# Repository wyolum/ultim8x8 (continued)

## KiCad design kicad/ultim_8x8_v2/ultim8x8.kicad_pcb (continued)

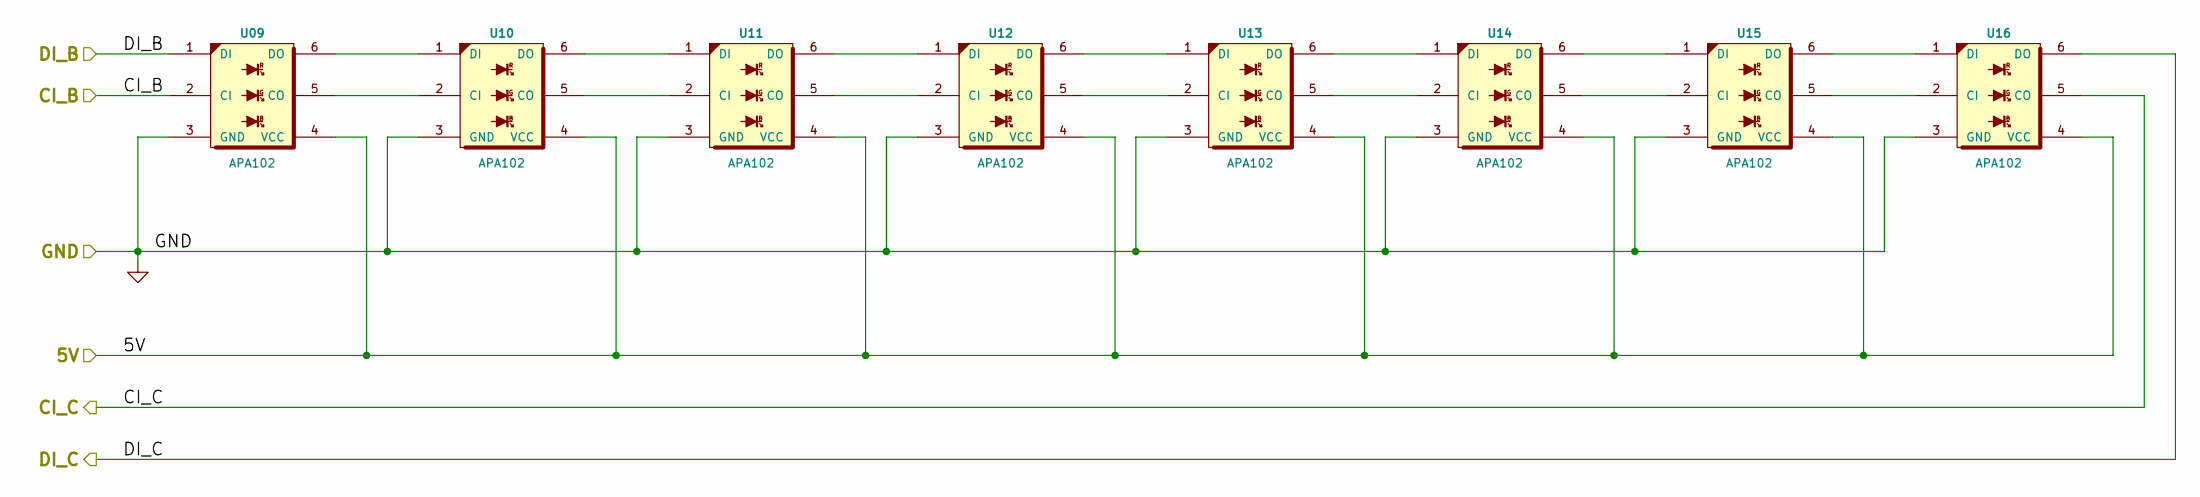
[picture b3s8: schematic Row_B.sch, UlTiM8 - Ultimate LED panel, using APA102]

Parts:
U09, U10, U11, U12, U13, U14, U15, U16: APA102

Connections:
/5V: U09.4 (VCC), U10.4 (VCC), U11.4 (VCC), U12.4 (VCC), U13.4 (VCC), U14.4 (VCC), U15.4 (VCC), U16.4 (VCC); also elsewhere on the board
/CI_B: U09.2 (CI); also elsewhere on the board
/CI_C: U16.5 (CO); also elsewhere on the board
/DI_B: U09.1 (DI); also elsewhere on the board
/DI_C: U16.6 (DO); also elsewhere on the board
GND: U09.3 (GND), U10.3 (GND), U11.3 (GND), U12.3 (GND), U13.3 (GND), U14.3 (GND), U15.3 (GND), U16.3 (GND); also elsewhere on the board
unnamed: U09.5 (CO), U10.2 (CI)
unnamed: U09.6 (DO), U10.1 (DI)
unnamed: U10.5 (CO), U11.2 (CI)
unnamed: U10.6 (DO), U11.1 (DI)
unnamed: U11.5 (CO), U12.2 (CI)
unnamed: U11.6 (DO), U12.1 (DI)
unnamed: U12.5 (CO), U13.2 (CI)
unnamed: U12.6 (DO), U13.1 (DI)
unnamed: U13.5 (CO), U14.2 (CI)
unnamed: U13.6 (DO), U14.1 (DI)
unnamed: U14.5 (CO), U15.2 (CI)
unnamed: U14.6 (DO), U15.1 (DI)
unnamed: U15.5 (CO), U16.2 (CI)
unnamed: U15.6 (DO), U16.1 (DI)

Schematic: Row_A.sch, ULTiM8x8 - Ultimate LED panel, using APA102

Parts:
C1: 100nF; c_0805
C2: 47uF 20V; c_2917
U01, U02, U03, U04, U07, U08: APA102
U05: APA102; APA102_U05
U06: APA102; APA102_U06

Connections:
/5V: C1.2, C2.1 (+), U01.4 (VCC), U02.4 (VCC), U03.4 (VCC), U04.4 (VCC), U05.4 (VCC), U06.4 (VCC), U07.4 (VCC), U08.4 (VCC); also elsewhere on the board
/CI_A: U01.2 (CI); also elsewhere on the board
/CI_B: U08.5 (CO); also elsewhere on the board
/DI_A: U01.1 (DI); also elsewhere on the board
/DI_B: U08.6 (DO); also elsewhere on the board
GND: C1.1, C2.2 (-), U01.3 (GND), U02.3 (GND), U03.3 (GND), U04.3 (GND), U05.3 (GND), U06.3 (GND), U07.3 (GND), U08.3 (GND); also elsewhere on the board
unnamed: U01.5 (CO), U02.2 (CI)
unnamed: U01.6 (DO), U02.1 (DI)
unnamed: U02.5 (CO), U03.2 (CI)
unnamed: U02.6 (DO), U03.1 (DI)
unnamed: U03.5 (CO), U04.2 (CI)
unnamed: U03.6 (DO), U04.1 (DI)
unnamed: U04.5 (CO), U05.2 (CI)
unnamed: U04.6 (DO), U05.1 (DI)
unnamed: U05.5 (CO), U06.2 (CI)
unnamed: U05.6 (DO), U06.1 (DI)
unnamed: U06.5 (CO), U07.2 (CI)
unnamed: U06.6 (DO), U07.1 (DI)
unnamed: U07.5 (CO), U08.2 (CI)
unnamed: U07.6 (DO), U08.1 (DI)

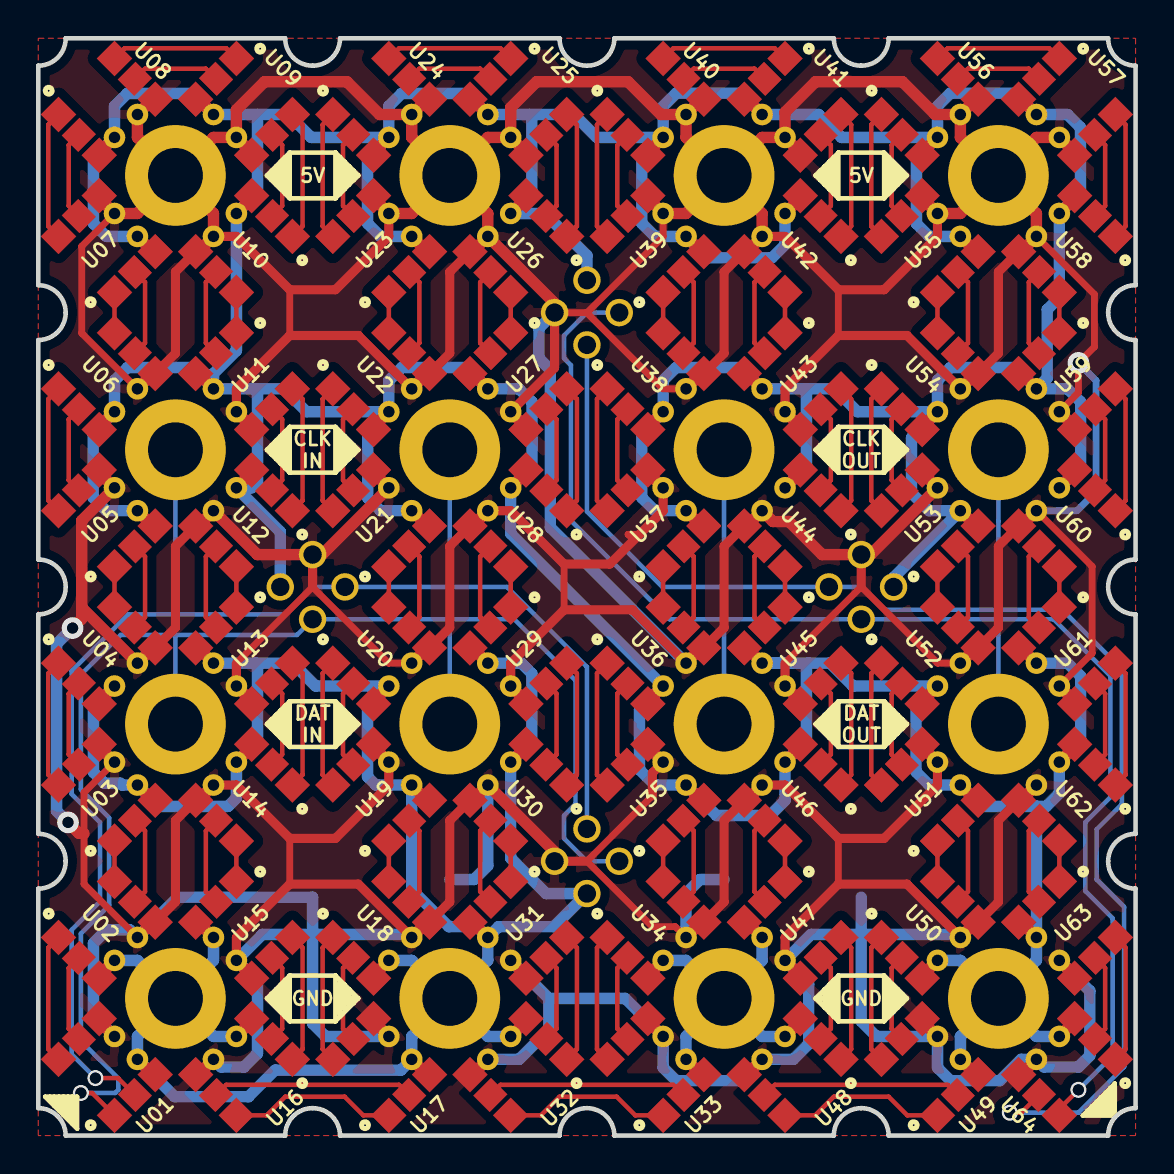
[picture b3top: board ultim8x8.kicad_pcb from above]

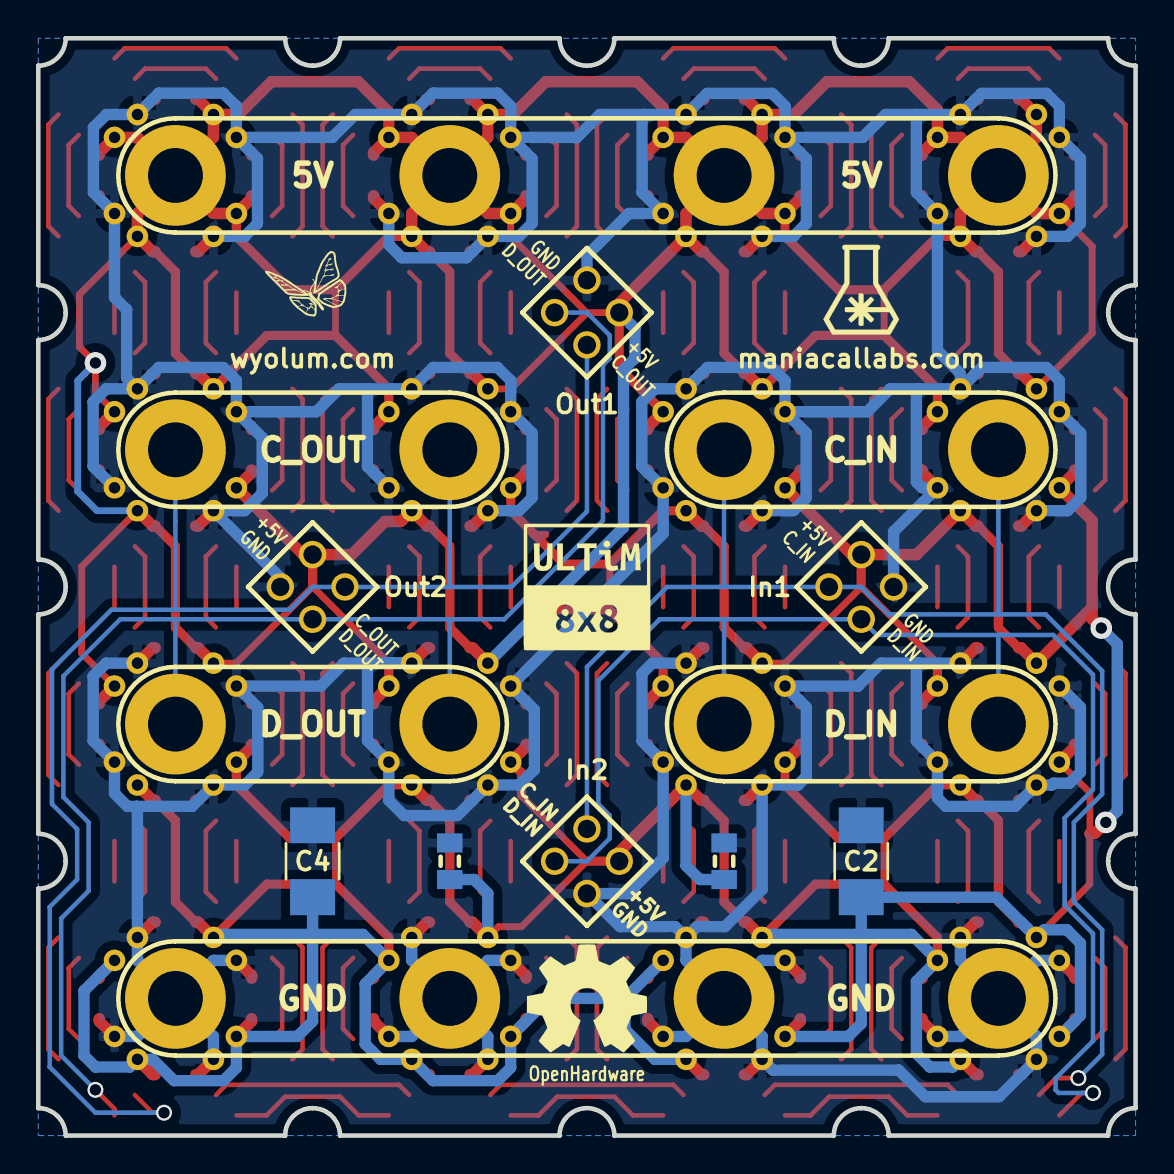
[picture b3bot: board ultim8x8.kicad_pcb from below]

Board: 2 copper layers, 61.0 x 61.0 mm, 92 parts (20 on the bottom side), 132 nets.

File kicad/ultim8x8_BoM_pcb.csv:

"Id";"Designator";"Package";"Quantity";"Designation";"Supplier and ref";
1;"L1";"logo_ultim8x8";1;"ULTiM8x8";;;
2;"P3";"PowerIn_stud";1;"5V";;;
3;"P4";"PowerIn_stud";1;"GND";;;
4;"C3,C1";"c_0805";2;"100nF";;;
5;"C2,C4";"c_2917";2;"47uF 20V";;;
6;"P6";"header_3pos_smd_male";1;"Output2";;;
7;"P5";"header_3pos_smd_male";1;"Input2";;;
8;"P2";"header_3pos_smd_male";1;"Output1";;;
9;"P1";"header_3pos_smd_male";1;"Input1";;;
10;"L2";"OSHW_6mm";1;"OSHW";;;
11;"L3";"logo_wyo_butterfly";1;"Wyolum";;;
12;"L4";"logo_MLlabs";1;"Maniacal Labs";;;
13;"U05";"APA102_U05";1;"APA102";;;
14;"U06";"APA102_U06";1;"APA102";;;
15;"U11";"APA102_U11";1;"APA102";;;
16;"U12";"APA102_U12";1;"APA102";;;
17;"U19";"APA102_U19";1;"APA102";;;
18;"U38";"APA102_U38";1;"APA102";;;
19;"U43";"APA102_U43";1;"APA102";;;
20;"U53";"APA102_U53";1;"APA102";;;
21;"U54";"APA102_U54";1;"APA102";;;
22;"U59";"APA102_U59";1;"APA102";;;
23;"U60";"APA102_U60";1;"APA102";;;
24;"U64,U49,U48,U33,U32,U17,U16,U01,U04,U02,U03,U07,U08,U09,U10,U13,U14,U15,U18,U20,U21,U22,U23,U24,U25,U26,U27,U28,U29,U30,U31,U34,U35,U36,U37,U39,U40,U41,U42,U44,U45,U46,U47,U50,U51,U52,U55,U56,U57,U58,U61,U62,U63";"APA102";53;"APA102";;;

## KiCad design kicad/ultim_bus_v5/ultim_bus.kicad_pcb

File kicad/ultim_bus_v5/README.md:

# ultim_bus

A PCB "bus bar" to allow three ultim8x8 modules to be connected easily. Mouse bites allow it to be snapped off easily. With some imagination, can be used to expand to larger matrices.

The first panel can be populated with a Huzzah. There are six SMD switches connected to 14, 12, 13, 15, 0, 16, 2 on the Huzzah, with pull up resistors (SMD 0805). Switch functions can be arbitrarily assigned in code.

License
-------
[CERN Open Hardware Licence v1.2 ]

[CERN Open Hardware Licence v1.2 ]:http://www.ohwr.org/attachments/2388/cern_ohl_v_1_2.txt

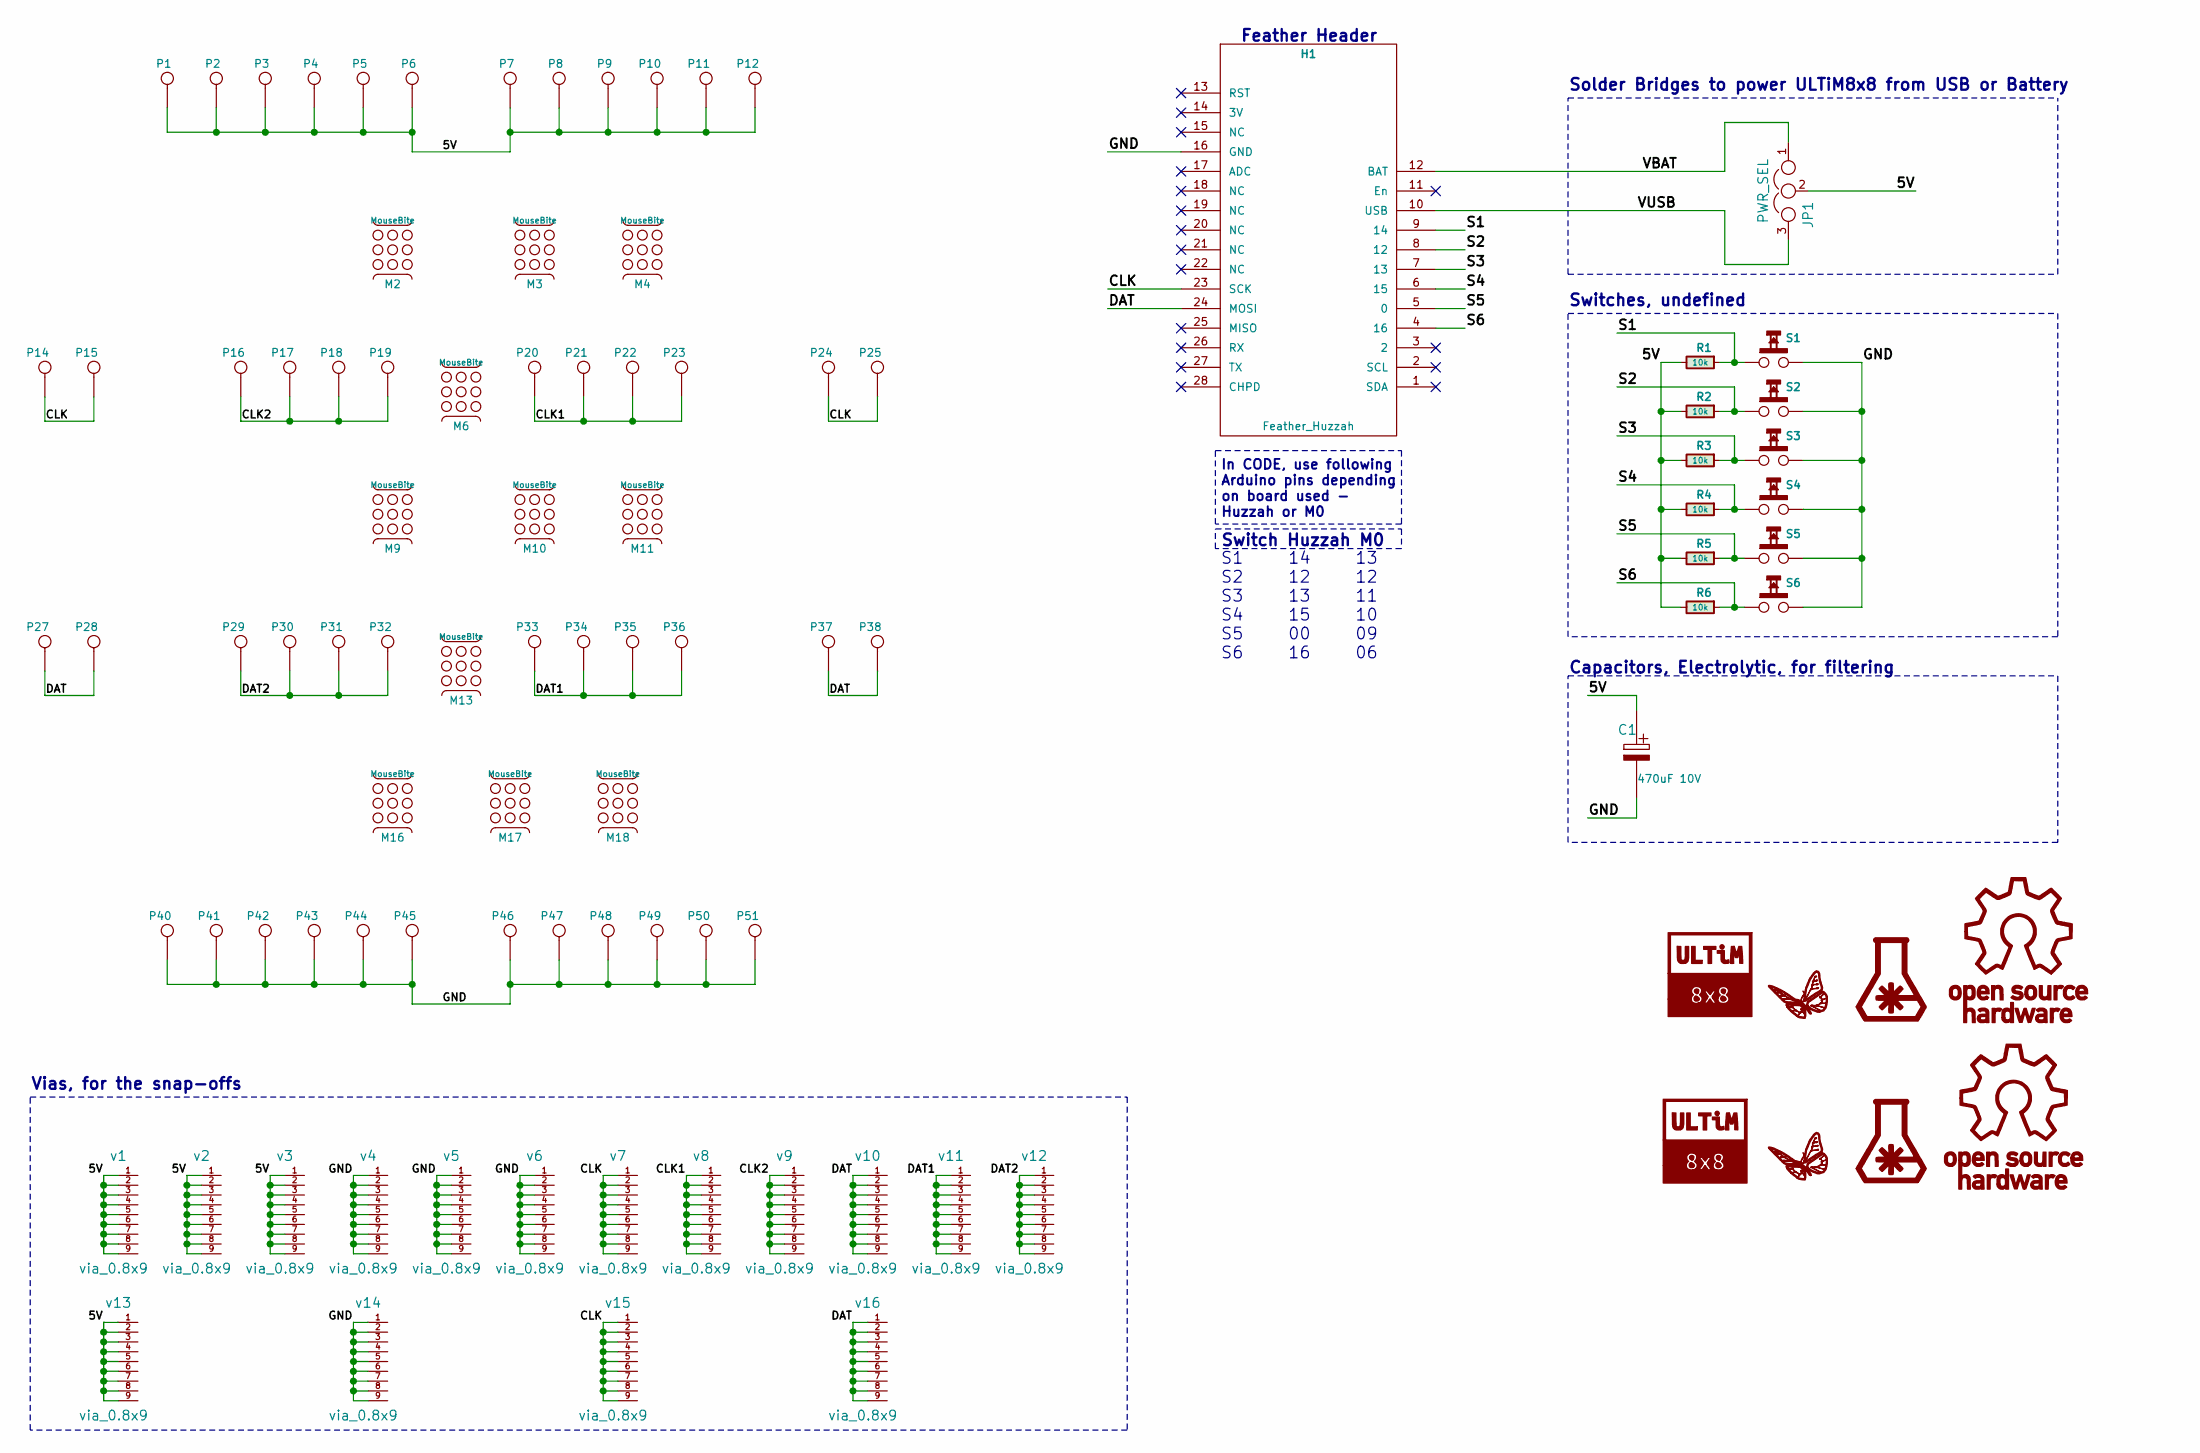
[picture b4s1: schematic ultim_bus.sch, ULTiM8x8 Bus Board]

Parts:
C1: 470uF 10V; cap_pol_rad3
H1: Feather_Huzzah; FEATHER_Huzzah
JP1: PWR_SEL; switch_spdt
L1, L2: OSHW; OSHW_6mm
L3, L4: LOGO_WL; logo_wyo_butterfly_small
L7, L8: LOGO_ML; logo_MLlabs_small
L11, L12: LOGO_U88; logo_ultim8x8_small
M2, M3, M4, M9, M10, M11, M16, M17, M18: MouseBite; mouse-bite-5.08mm-slot
M6, M13: MouseBite; mouse-bite-2.54mm-slot
P1, P4, P5, P8, P9, P12, P15, P16, P19, P20, P23, P24, P28, P29, P32, P33, P36, P37, P40, P43, P44, P47, P48, P51: CONN_1; Screw_SqPad
P2, P3, P6, P7, P10, P11, P14, P17, P18, P21, P22, P25, P27, P30, P31, P34, P35, P38, P41, P42, P45, P46, P49, P50: CONN_1; Screw
R1, R2, R3, R4, R5, R6: 10k; r_0805
S1, S2, S3, S4, S5, S6: SPST-M-2; SW-PB
v1, v2, v3, v4, v5, v6, v7, v8, v9, v10, v11, v12, v13, v14, v15, v16: via_0.8x9

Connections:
/5V: C1.1 (+), JP1.2, P1.1, P2.1, P3.1, P4.1, P5.1, P6.1, P7.1, P8.1, P9.1, P10.1, P11.1, P12.1, R1.2, R2.2, R3.2, R4.2, R5.2, R6.2, v1.1, v1.2, v1.3, v1.4, v1.5, v1.6, v1.7, v1.8, v1.9, v2.1, v2.2, v2.3, v2.4, v2.5, v2.6, v2.7, v2.8, v2.9, v3.1, v3.2, v3.3, v3.4, v3.5, v3.6, v3.7, v3.8, v3.9, v13.1, v13.2, v13.3, v13.4, v13.5, v13.6, v13.7, v13.8, v13.9
/CLK: H1.23 (SCK), P14.1, P15.1, P24.1, P25.1, v7.1, v7.2, v7.3, v7.4, v7.5, v7.6, v7.7, v7.8, v7.9, v15.1, v15.2, v15.3, v15.4, v15.5, v15.6, v15.7, v15.8, v15.9
/CLK1: P20.1, P21.1, P22.1, P23.1, v8.1, v8.2, v8.3, v8.4, v8.5, v8.6, v8.7, v8.8, v8.9
/CLK2: P16.1, P17.1, P18.1, P19.1, v9.1, v9.2, v9.3, v9.4, v9.5, v9.6, v9.7, v9.8, v9.9
/DAT: H1.24 (MOSI), P27.1, P28.1, P37.1, P38.1, v10.1, v10.2, v10.3, v10.4, v10.5, v10.6, v10.7, v10.8, v10.9, v16.1, v16.2, v16.3, v16.4, v16.5, v16.6, v16.7, v16.8, v16.9
/DAT1: P33.1, P34.1, P35.1, P36.1, v11.1, v11.2, v11.3, v11.4, v11.5, v11.6, v11.7, v11.8, v11.9
/DAT2: P29.1, P30.1, P31.1, P32.1, v12.1, v12.2, v12.3, v12.4, v12.5, v12.6, v12.7, v12.8, v12.9
/GND: C1.2 (-), H1.16 (GND), P40.1, P41.1, P42.1, P43.1, P44.1, P45.1, P46.1, P47.1, P48.1, P49.1, P50.1, P51.1, S1.2, S2.2, S3.2, S4.2, S5.2, S6.2, v4.1, v4.2, v4.3, v4.4, v4.5, v4.6, v4.7, v4.8, v4.9, v5.1, v5.2, v5.3, v5.4, v5.5, v5.6, v5.7, v5.8, v5.9, v6.1, v6.2, v6.3, v6.4, v6.5, v6.6, v6.7, v6.8, v6.9, v14.1, v14.2, v14.3, v14.4, v14.5, v14.6, v14.7, v14.8, v14.9
/S1: H1.9 (14), R1.1, S1.1
/S2: H1.8 (12), R2.1, S2.1
/S3: H1.7 (13), R3.1, S3.1
/S4: H1.6 (15), R4.1, S4.1
/S5: H1.5 (0), R5.1, S5.1
/S6: H1.4 (16), R6.1, S6.1
/VBAT: H1.12 (BAT), JP1.1
/VUSB: H1.10 (USB), JP1.3

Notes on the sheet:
Solder Bridges to power ULTiM8x8 from USB or Battery
Feather Header
Switches, undefined
Vias, for the snap-offs
Capacitors, Electrolytic, for filtering
Switch Huzzah M0
S1 14 13 S2 12 12 S3 13 11 S4 15 10 S5 00 09 S6 16 06
In CODE, use following Arduino pins depending on board used - Huzzah or M0

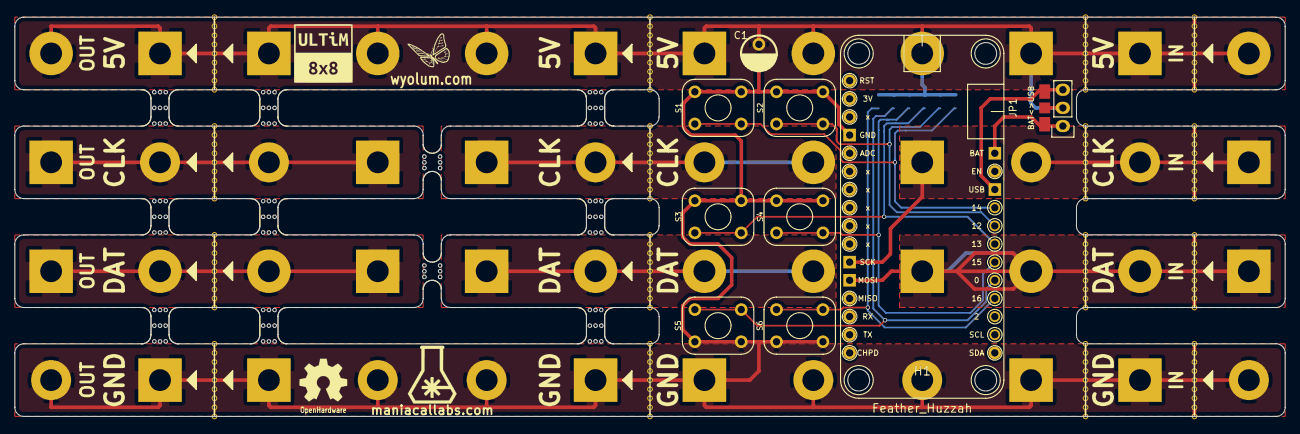
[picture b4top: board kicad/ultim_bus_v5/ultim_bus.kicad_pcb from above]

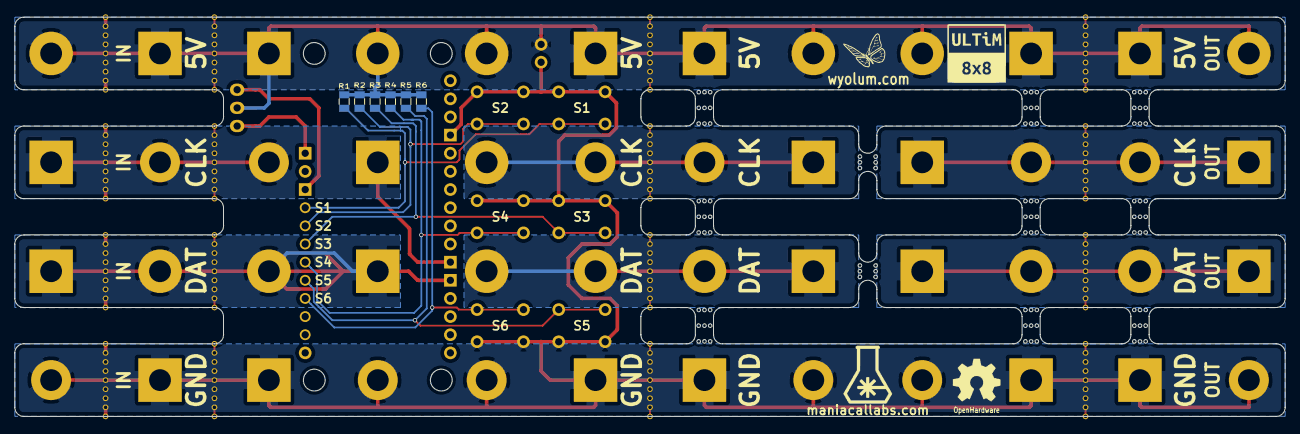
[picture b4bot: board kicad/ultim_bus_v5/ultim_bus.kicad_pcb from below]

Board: 2 copper layers, 177.8 x 55.9 mm, 98 parts (10 on the bottom side), 16 nets.

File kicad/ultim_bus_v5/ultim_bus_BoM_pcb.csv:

"Id";"Designator";"Package";"Quantity";"Designation";"Supplier and ref";
1;"M13,M6";"mouse-bite-2.54mm-slot";2;"MouseBite";;;
2;"L8,L7";"logo_MLlabs_small";2;"LOGO_ML";;;
3;"P31,P38,P35,P34,P30,P27,P2,P3,P6,P7,P10,P11,P14,P17,P18,P21,P22,P25,P41,P42,P45,P46,P49,P50";"Screw";24;"CONN_1";;;
4;"L4,L3";"logo_wyo_butterfly_small";2;"LOGO_WL";;;
5;"L11,L12";"logo_ultim8x8_small";2;"LOGO_U88";;;
6;"L2,L1";"OSHW_6mm";2;"OSHW";;;
7;"P1,P4,P5,P8,P9,P12,P28,P29,P32,P33,P36,P37,P15,P16,P19,P20,P23,P24,P40,P43,P44,P47,P48,P51";"Screw_SqPad";24;"CONN_1";;;
8;"M2,M9,M16";"mouse-bite-5.08mm-slot";3;"MouseBite";;;
9;"JP1";"switch_spdt";1;"PWR_SEL";;;
10;"v1,v2,v3,v4,v5,v6,v7,v8,v9,v10,v11,v12,v13,v14,v15,v16";"via_0.8x9";16;"via_0.8x9";;;
11;"M3,M4,M10,M11,M17,M18";"mouse-bite-5.08mm-slot";6;"MouseBite";;;
12;"S2,S1,S3,S4,S5,S6";"SW_SMD";6;"SPST-M-2";;;
13;"R6,R5,R4,R3,R2,R1";"r_0805";6;"10k";;;
14;"C1";"cap_pol_rad3";1;"470uF 10V";;;
15;"H1";"FEATHER_M0_2";1;"Feather_M0";;;

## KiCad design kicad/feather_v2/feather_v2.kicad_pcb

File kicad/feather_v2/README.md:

# feather_v2

An add-on board to the Ultim8x8 LED Matrix for mounting an Adafruit Feather.

Use 4 pin male headers on ultim8x8 at either of two possible locations -- Input1/Output1 or Input2/Output2

Use a 2.54mm pitch slide switch/header+jumper mounted either at JP1 or JP2, to select between USB supply or BAT (external LiPo).

Instead of using a Switch, use shorting pads near the switch pads to permanently select one of the two supply options - USB or BAT.

License
-------
[CERN Open Hardware Licence v1.2 ]

[CERN Open Hardware Licence v1.2 ]:http://www.ohwr.org/attachments/2388/cern_ohl_v_1_2.txt

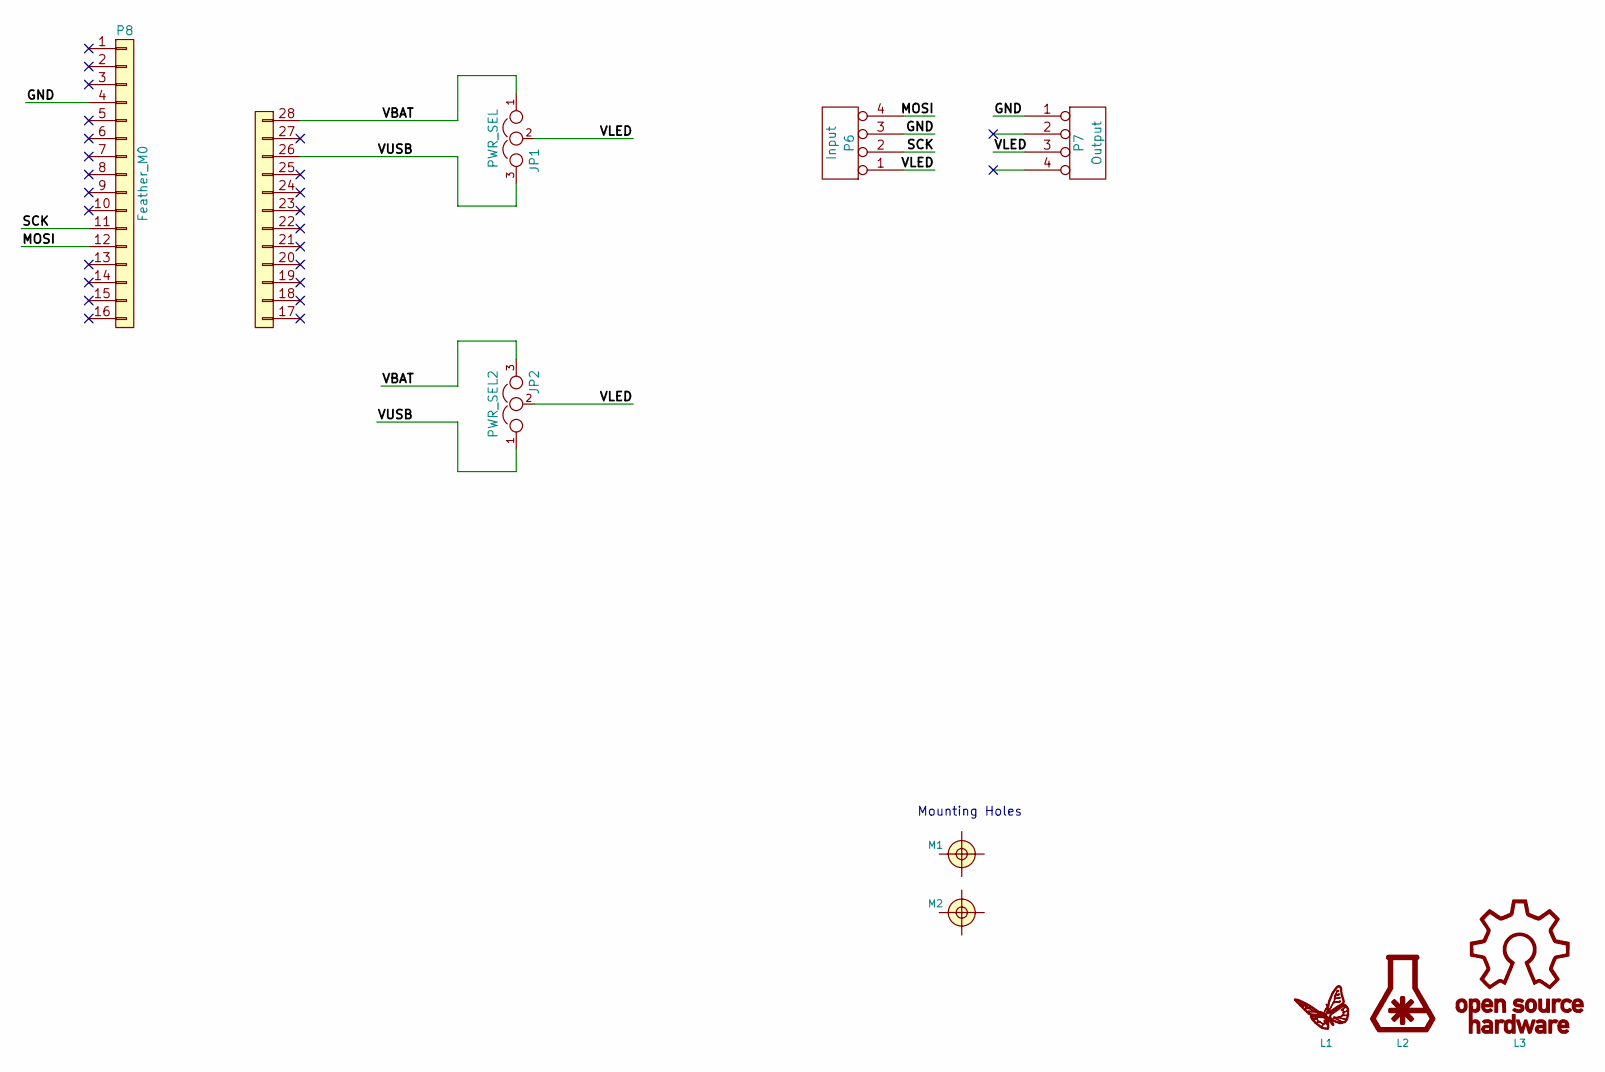
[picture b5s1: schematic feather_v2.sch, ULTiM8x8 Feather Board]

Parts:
JP1: PWR_SEL; switch_spdt
JP2: PWR_SEL2; switch_spdt
L1: LOGO_WL; logo_wyo_butterfly_small
L2: LOGO_ML; logo_MLlabs_small
L3: OSHW; OSHW_6mm
M1, M2: Screw; Screw_NPTH
P6: Input; header_2x2pos_th_male
P7: Output; header_2x2pos_th_male
P8: Feather_M0; FEATHER_M0

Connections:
/GND: P6.3, P7.1, P8.4
/MOSI: P6.4, P8.12
/SCK: P6.2, P8.11
/VBAT: JP1.1, JP2.3, P8.28
/VLED: JP1.2, JP2.2, P6.1, P7.3
/VUSB: JP1.3, JP2.1, P8.26

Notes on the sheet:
Mounting Holes

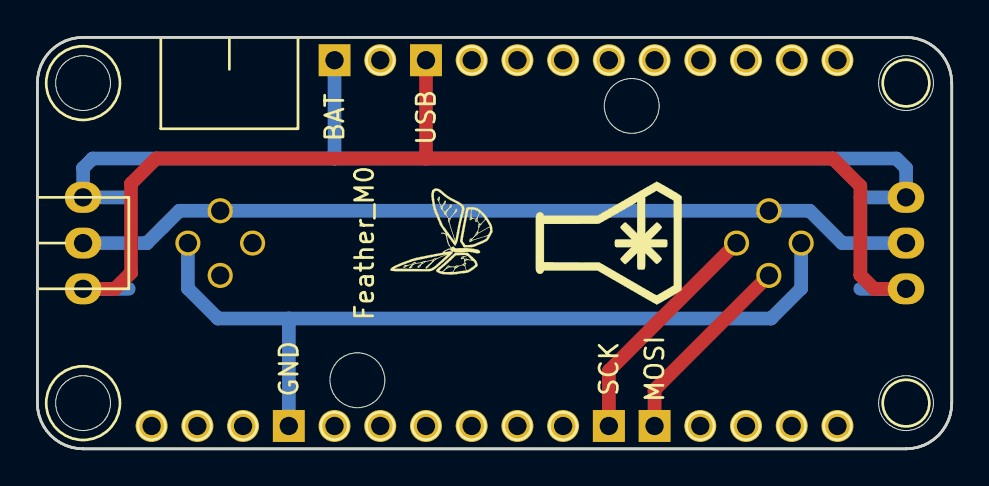
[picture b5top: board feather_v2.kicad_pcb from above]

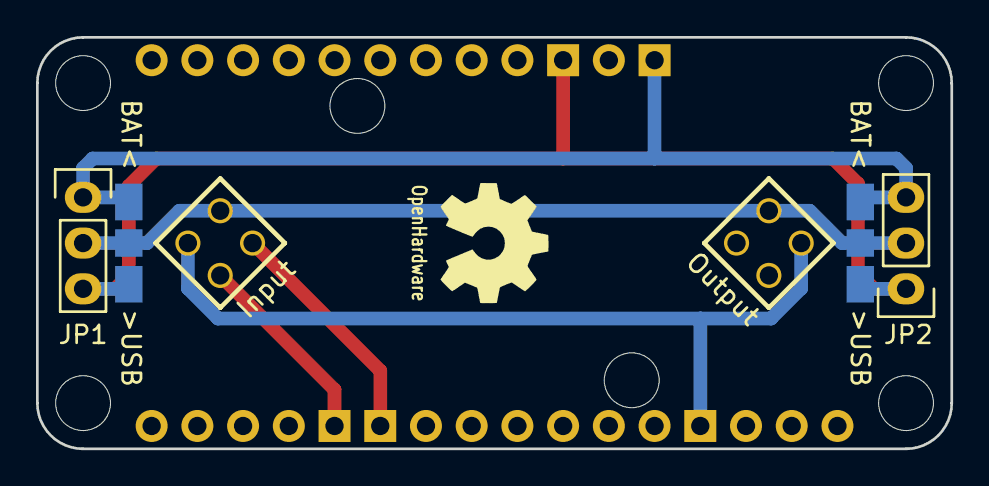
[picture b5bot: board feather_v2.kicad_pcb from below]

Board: 2 copper layers, 50.8 x 22.9 mm, 10 parts (5 on the bottom side), 6 nets.

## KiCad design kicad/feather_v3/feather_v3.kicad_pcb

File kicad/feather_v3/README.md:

# feather_v3

An add-on board to the Ultim8x8 LED Matrix for mounting an Adafruit Feather M0.

Use 4 pin male headers on ultim8x8 at either of two possible locations -- Input1/Output1 or Input2/Output2

Use a 2.54mm pitch slide switch/header+jumper mounted either at JP1 or JP2, to select between USB supply or BAT (external LiPo).

Instead of using a Switch, use shorting pads near the switch pads to permanently select one of the two supply options - USB or BAT.

License
-------
[CERN Open Hardware Licence v1.2 ]

[CERN Open Hardware Licence v1.2 ]:http://www.ohwr.org/attachments/2388/cern_ohl_v_1_2.txt

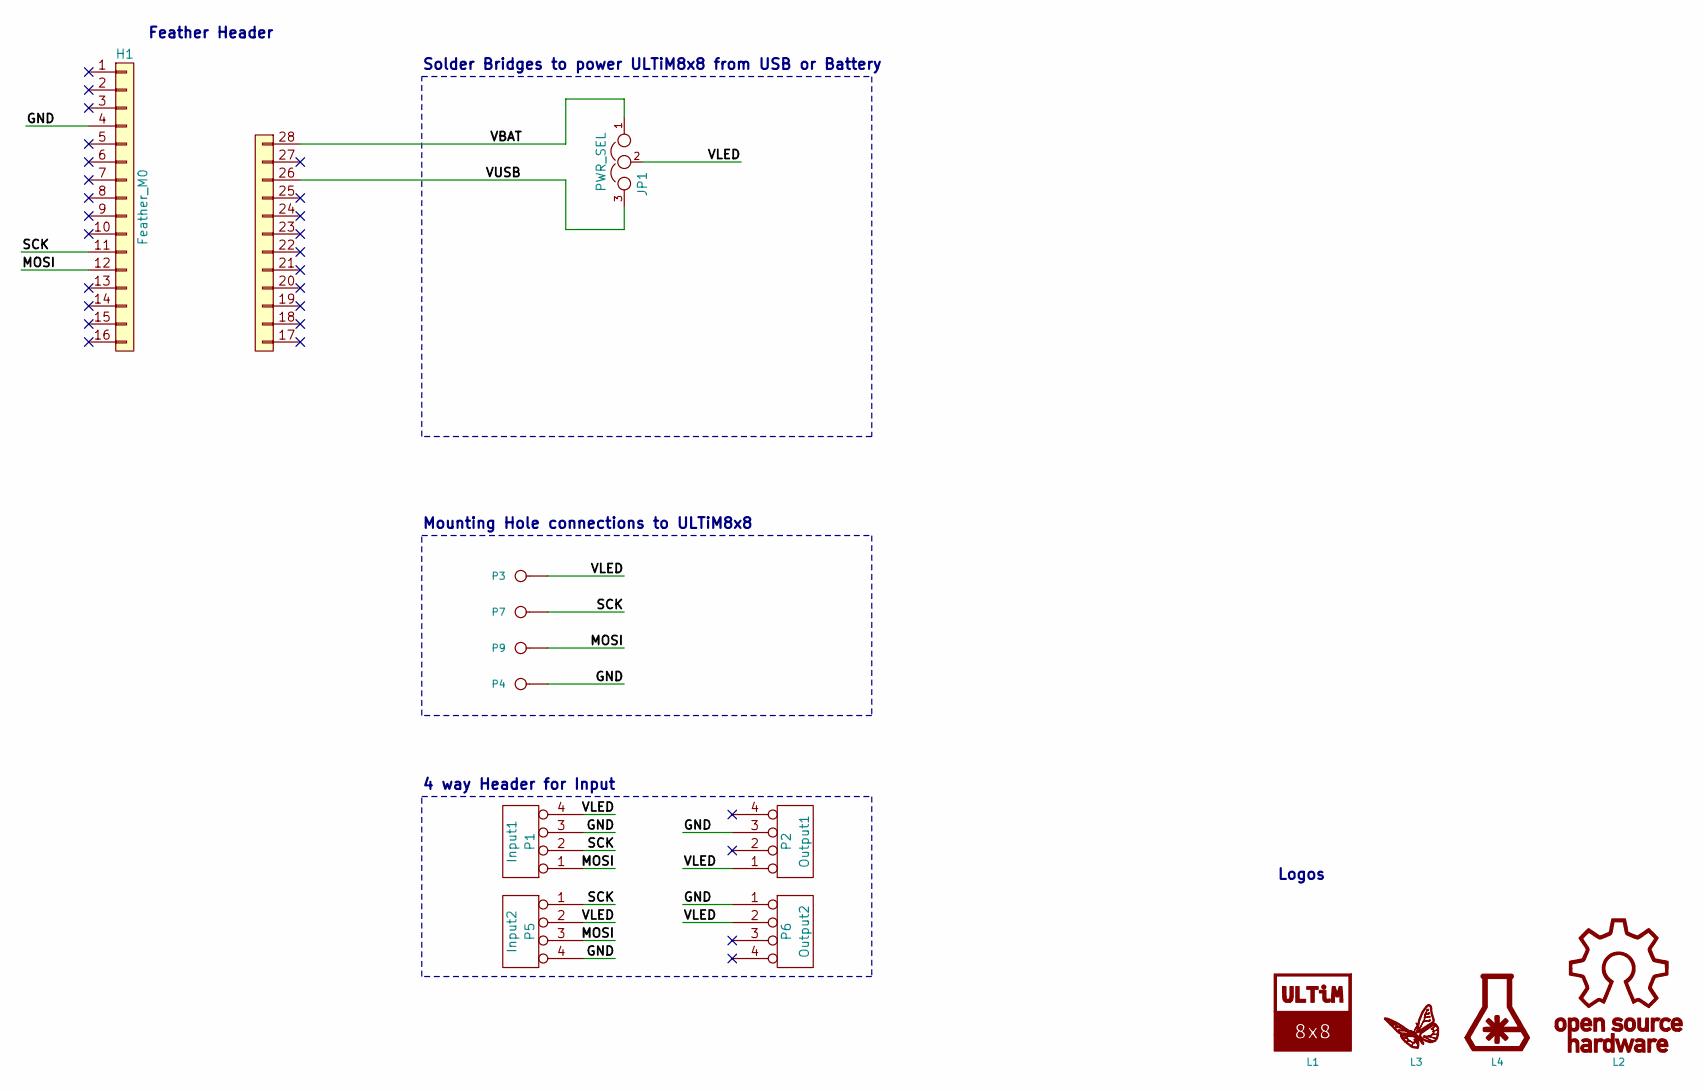
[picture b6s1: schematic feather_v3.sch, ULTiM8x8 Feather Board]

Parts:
H1: Feather_M0; FEATHER_M0_2
JP1: PWR_SEL; switch_spdt
L1: LOGO_U88; logo_ultim8x8_small
L2: OSHW; OSHW_6mm
L3: LOGO_WL; logo_wyo_butterfly_small
L4: LOGO_ML; logo_MLlabs_small
P1: Input1; header_2x2pos_th_male
P2: Output1; header_2x2pos_th_male
P3: 5V; Screw
P4: GND; Screw
P5: Input2; header_2x2pos_th_male
P6: Output2; header_2x2pos_th_male
P7: CI_A; Screw
P9: DI_A; Screw

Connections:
/GND: H1.4, P1.3, P2.3, P4.1, P5.4, P6.1
/MOSI: H1.12, P1.1, P5.3, P9.1
/SCK: H1.11, P1.2, P5.1, P7.1
/VBAT: H1.28, JP1.1
/VLED: JP1.2, P1.4, P2.1, P3.1, P5.2, P6.2
/VUSB: H1.26, JP1.3

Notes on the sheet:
Mounting Hole connections to ULTiM8x8
4 way Header for Input
Solder Bridges to power ULTiM8x8 from USB or Battery
Feather Header
Logos

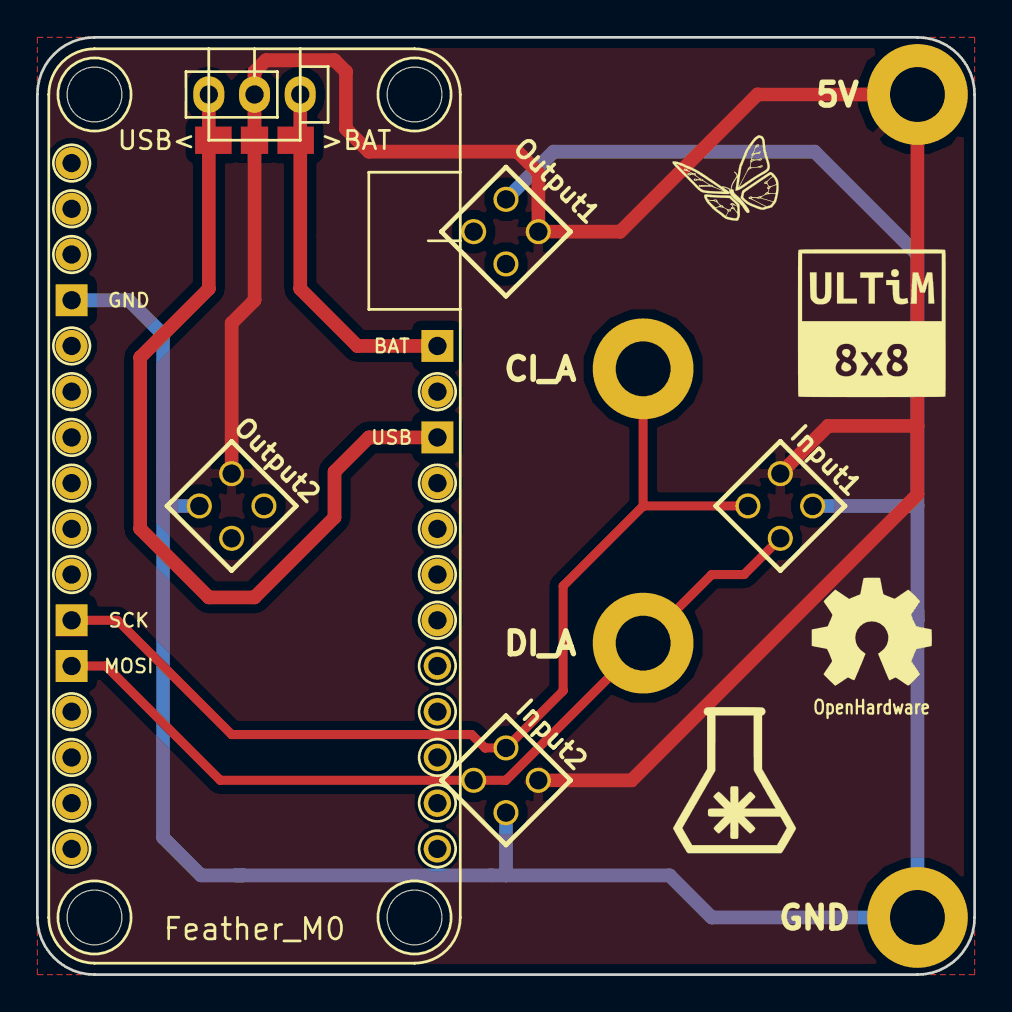
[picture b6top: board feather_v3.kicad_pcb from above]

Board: 2 copper layers, 52.1 x 52.1 mm, 14 parts (0 on the bottom side), 6 nets.
